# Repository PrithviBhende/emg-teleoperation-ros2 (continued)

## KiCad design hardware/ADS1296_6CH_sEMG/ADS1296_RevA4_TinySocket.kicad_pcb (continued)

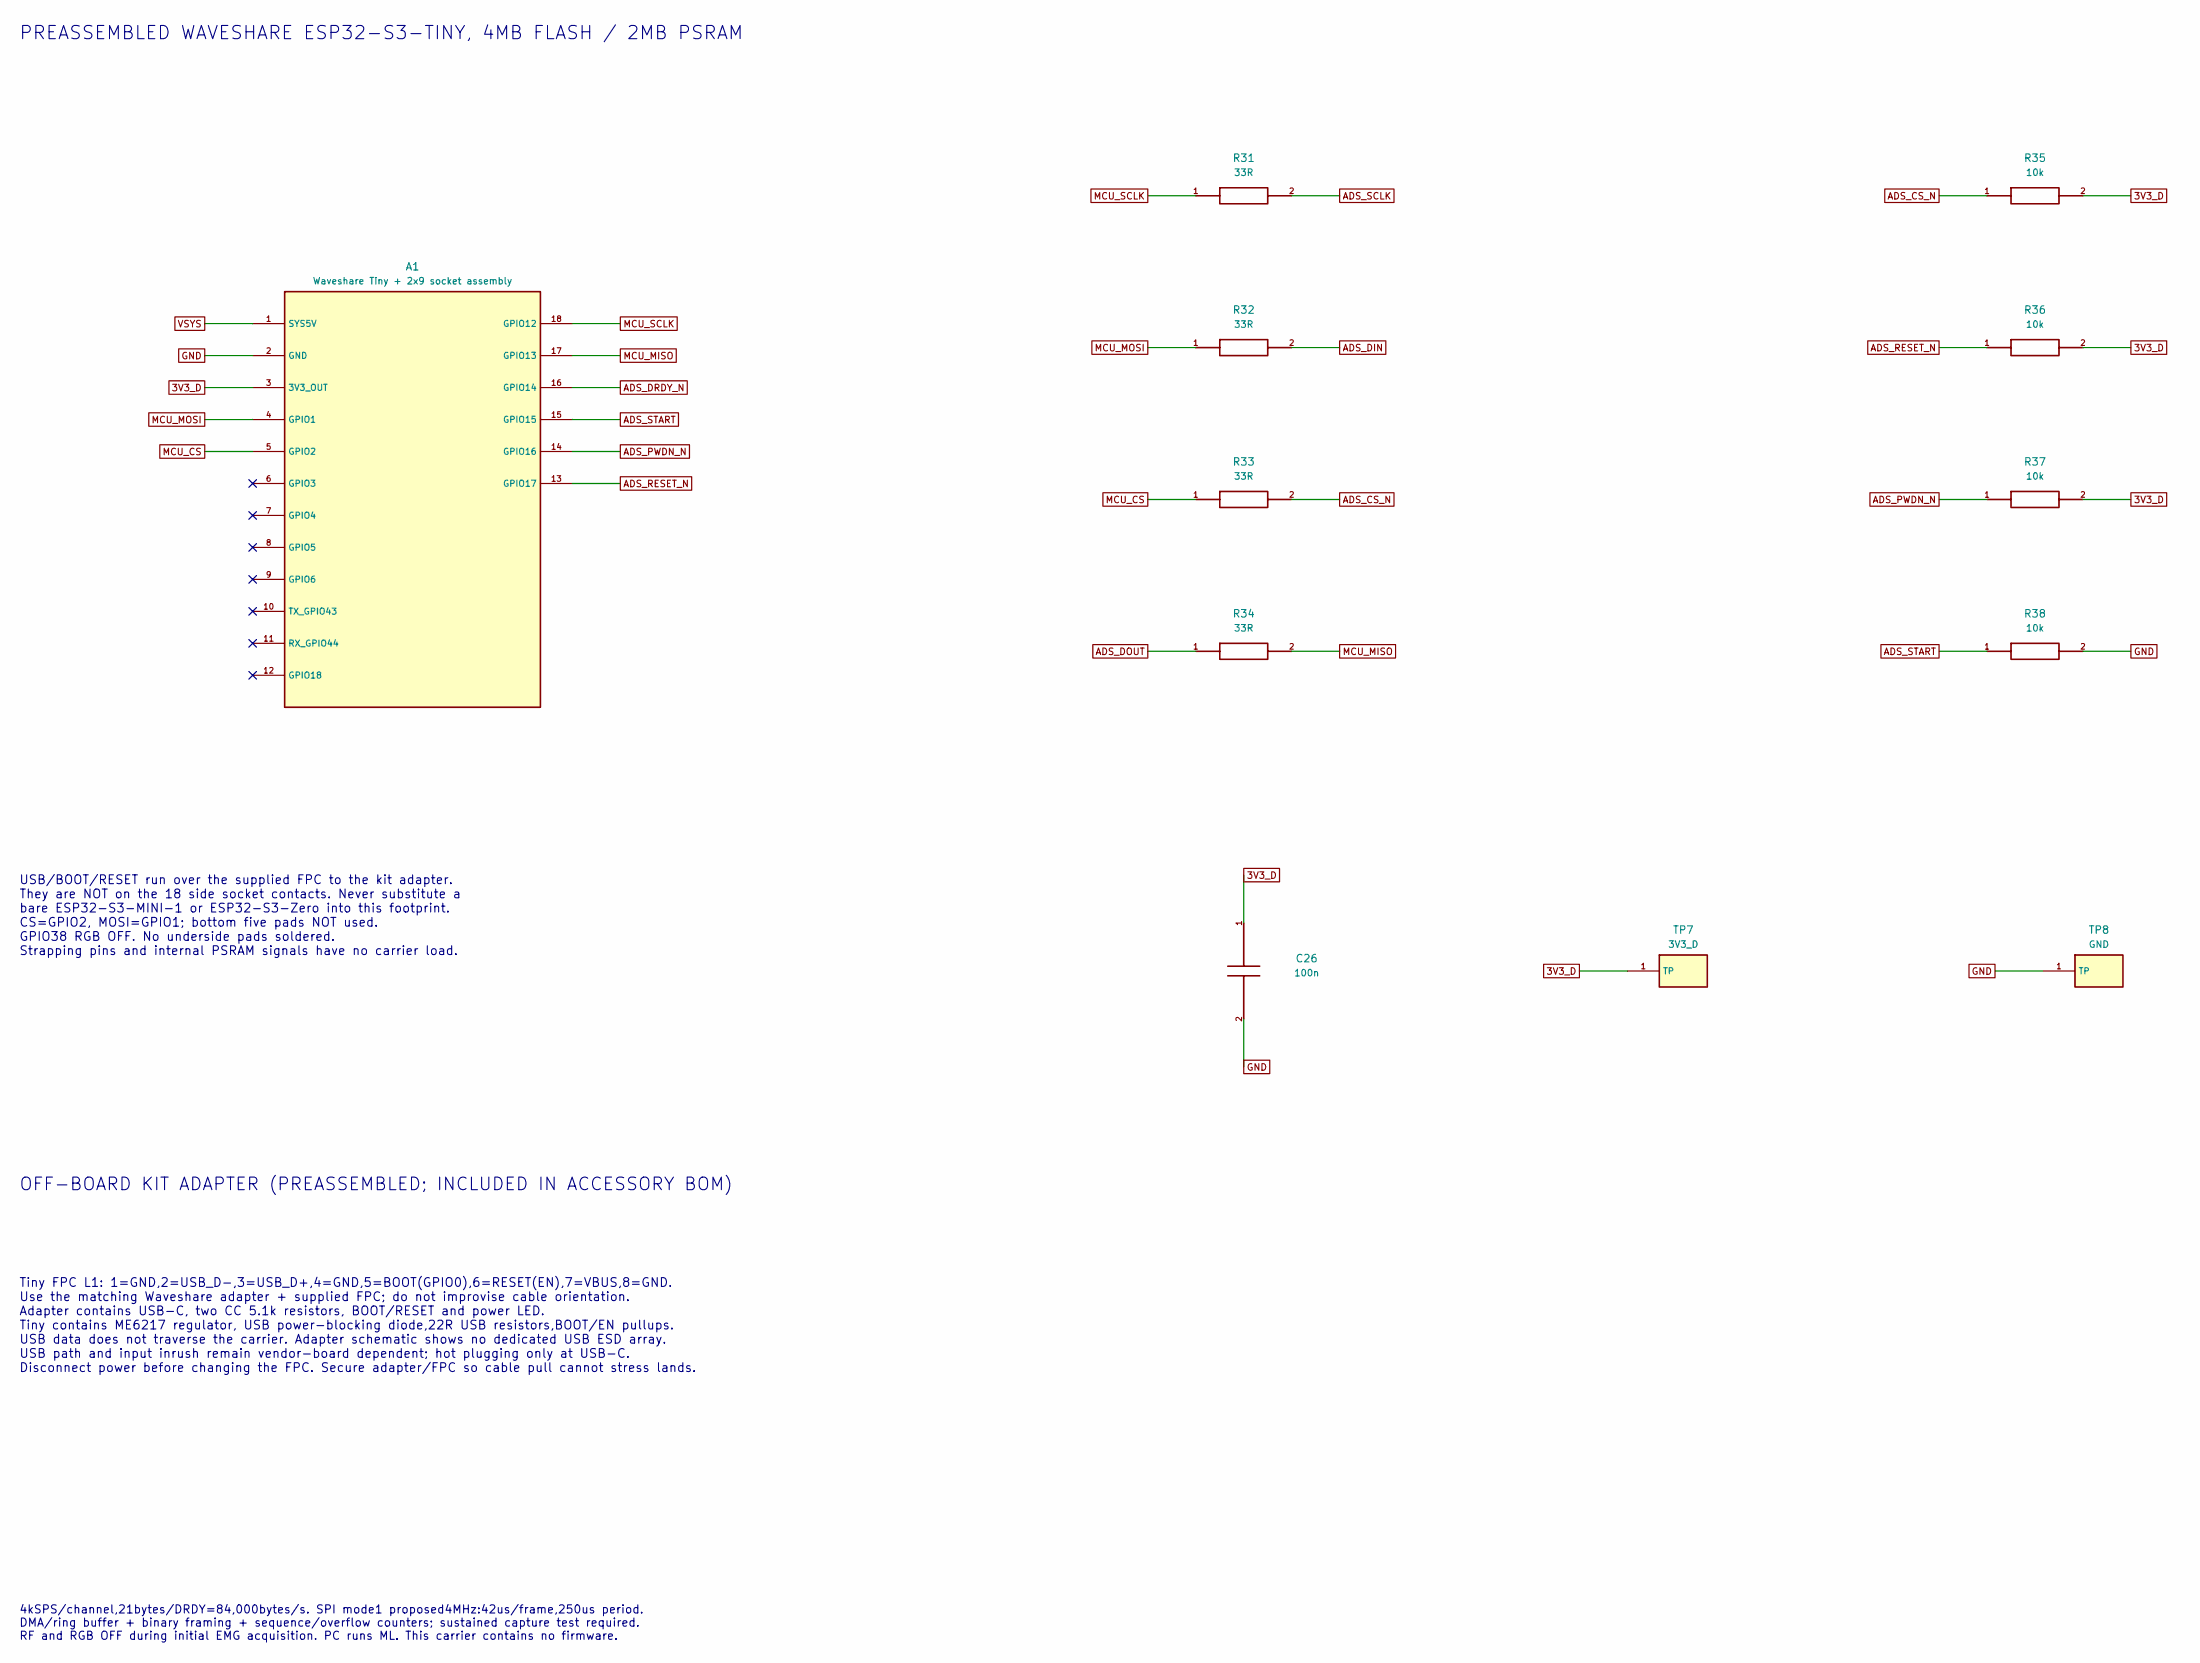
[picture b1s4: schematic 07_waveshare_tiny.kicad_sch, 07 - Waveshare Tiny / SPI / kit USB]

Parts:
A1: Waveshare Tiny + 2x9 socket assembly; Waveshare_ESP32_S3_Tiny_Socket18; MPN ESP32-S3-Tiny-Kit (27070)
C26: 100n; C_0805_2012Metric; MPN C0805C104K4RACTU
R31, R32, R33, R34: 33R; R_0805_2012Metric; MPN RC0805FR-0733RL
R35, R36, R37, R38: 10k; R_0805_2012Metric; MPN RC0805FR-0710KL
TP7: 3V3_D; TestPoint_Pad_D1.5mm
TP8: GND; TestPoint_Pad_D1.5mm

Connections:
3V3_D: A1.3 (3V3_OUT), C26.1, R35.2, R36.2, R37.2, TP7.1; also elsewhere on the board
ADS_CS_N: R33.2, R35.1; also elsewhere on the board
ADS_DIN: R32.2; also elsewhere on the board
ADS_DOUT: R34.1; also elsewhere on the board
ADS_DRDY_N: A1.16 (GPIO14); also elsewhere on the board
ADS_PWDN_N: A1.14 (GPIO16), R37.1; also elsewhere on the board
ADS_RESET_N: A1.13 (GPIO17), R36.1; also elsewhere on the board
ADS_SCLK: R31.2; also elsewhere on the board
ADS_START: A1.15 (GPIO15), R38.1; also elsewhere on the board
GND: A1.2 (GND), C26.2, R38.2, TP8.1; also elsewhere on the board
MCU_CS: A1.5 (GPIO2), R33.1
MCU_MISO: A1.17 (GPIO13), R34.2
MCU_MOSI: A1.4 (GPIO1), R32.1
MCU_SCLK: A1.18 (GPIO12), R31.1
VSYS: A1.1 (SYS5V); also elsewhere on the board

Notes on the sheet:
PREASSEMBLED WAVESHARE ESP32-S3-TINY, 4MB FLASH / 2MB PSRAM
USB/BOOT/RESET run over the supplied FPC to the kit adapter. They are NOT on the 18 side socket contacts. Never substitute a bare ESP32-S3-MINI-1 or ESP32-S3-Zero into this footprint. CS=GPIO2, MOSI=GPIO1; bottom five pads NOT used. GPIO38 RGB OFF. No underside pads soldered. Strapping pins and int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
OFF-BOARD KIT ADAPTER (PREASSEMBLED; INCLUDED IN ACCESSORY BOM)
Tiny FPC L1: 1=GND,2=USB_D-,3=USB_D+,4=GND,5=BOOT(GPIO0),6=RESET(EN),7=VBUS,8=GND. Use the matching Waveshare adapter + supplied FPC; do not improvise cable orientation. Adapter contains USB-C, two CC 5.1k resistors, BOOT/RESET and power LED. Tiny contains ME6217 regulator, USB power-blocking diode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
4kSPS/channel,21bytes/DRDY=84,000bytes/s. SPI mode1 proposed4MHz:42us/frame,250us period. DMA/ring buffer + binary framing + sequence/overflow counters; sustained capture test required. RF and RGB OFF during initial EMG acquisition. PC runs ML. This carrier contains no firmware.

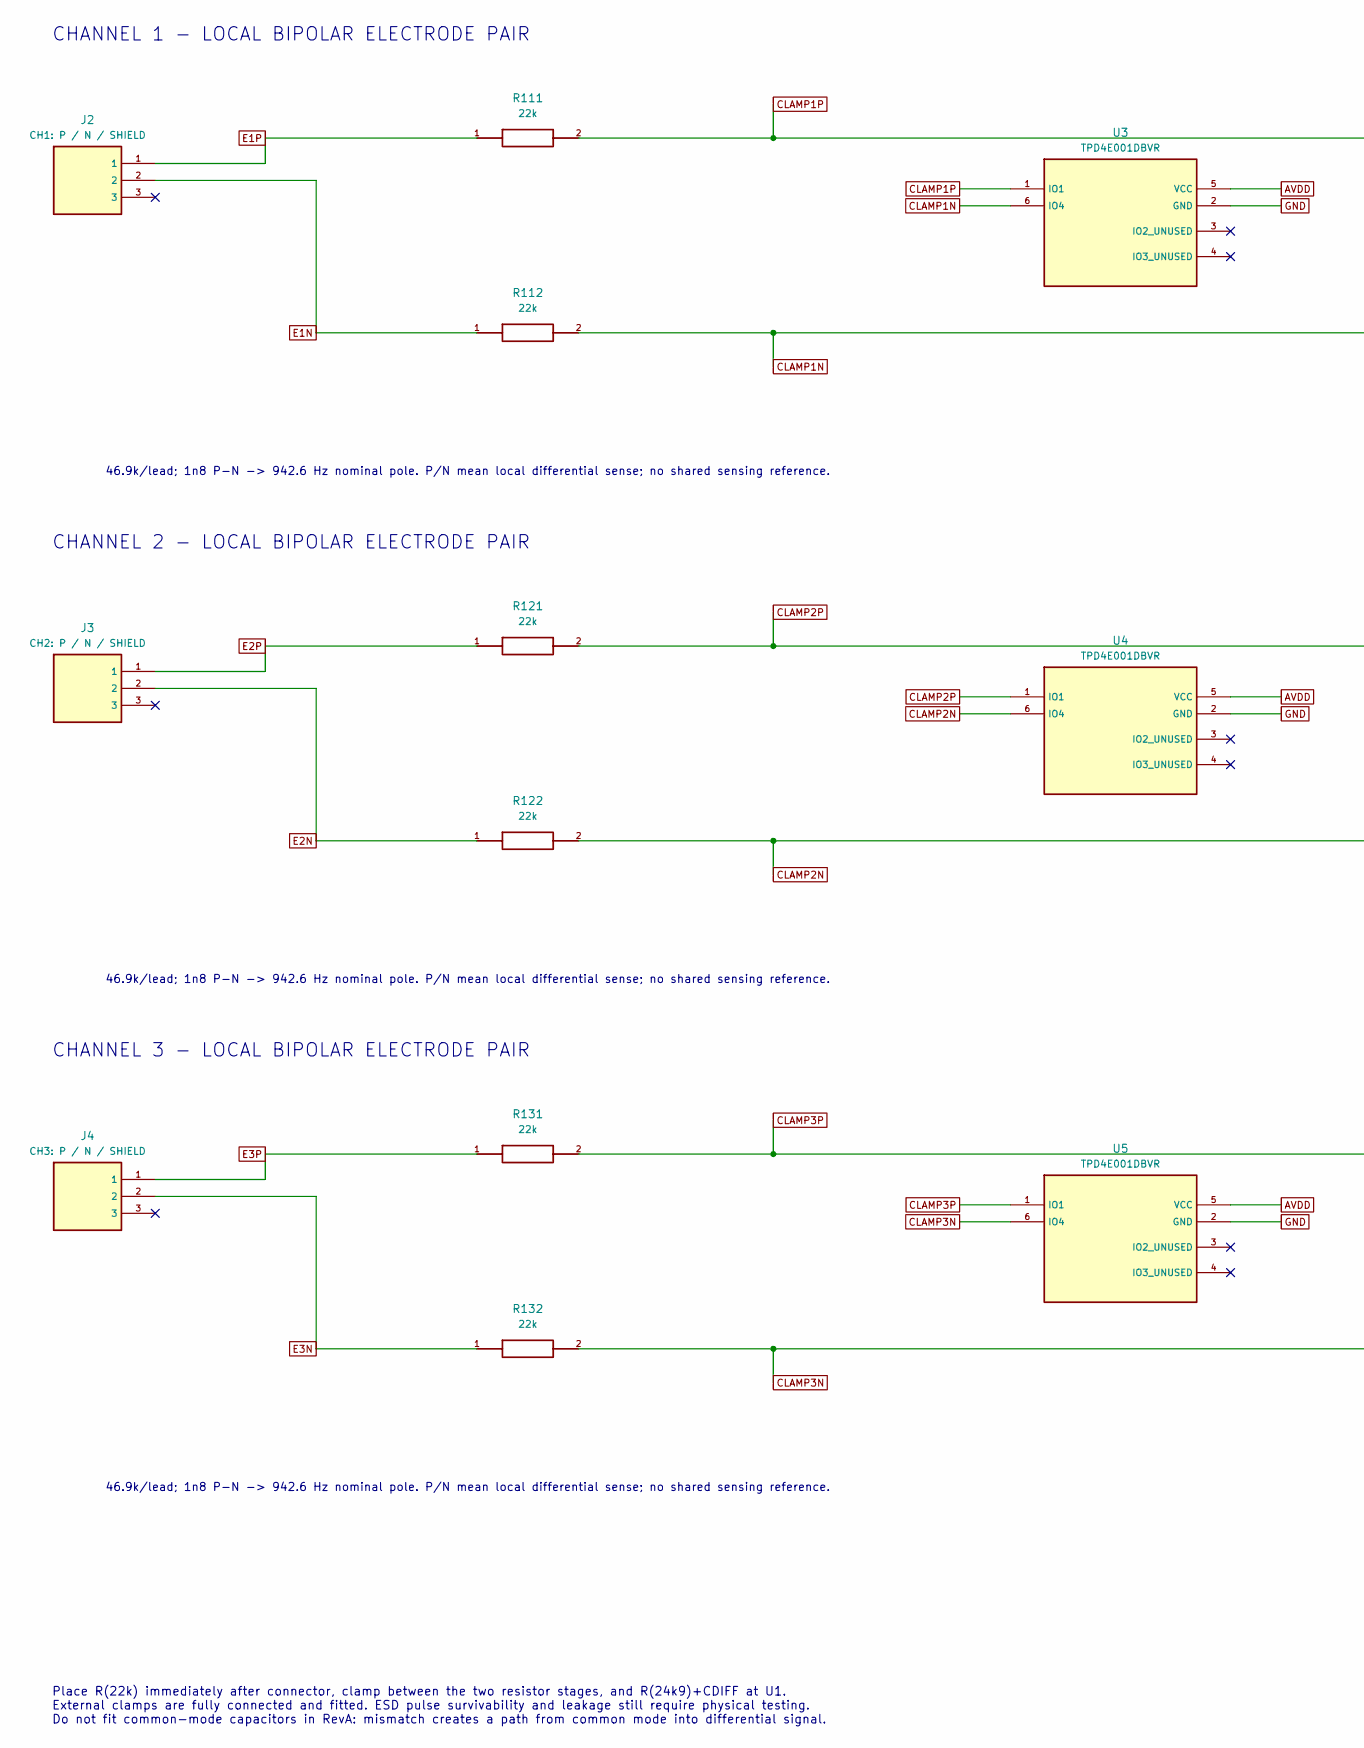
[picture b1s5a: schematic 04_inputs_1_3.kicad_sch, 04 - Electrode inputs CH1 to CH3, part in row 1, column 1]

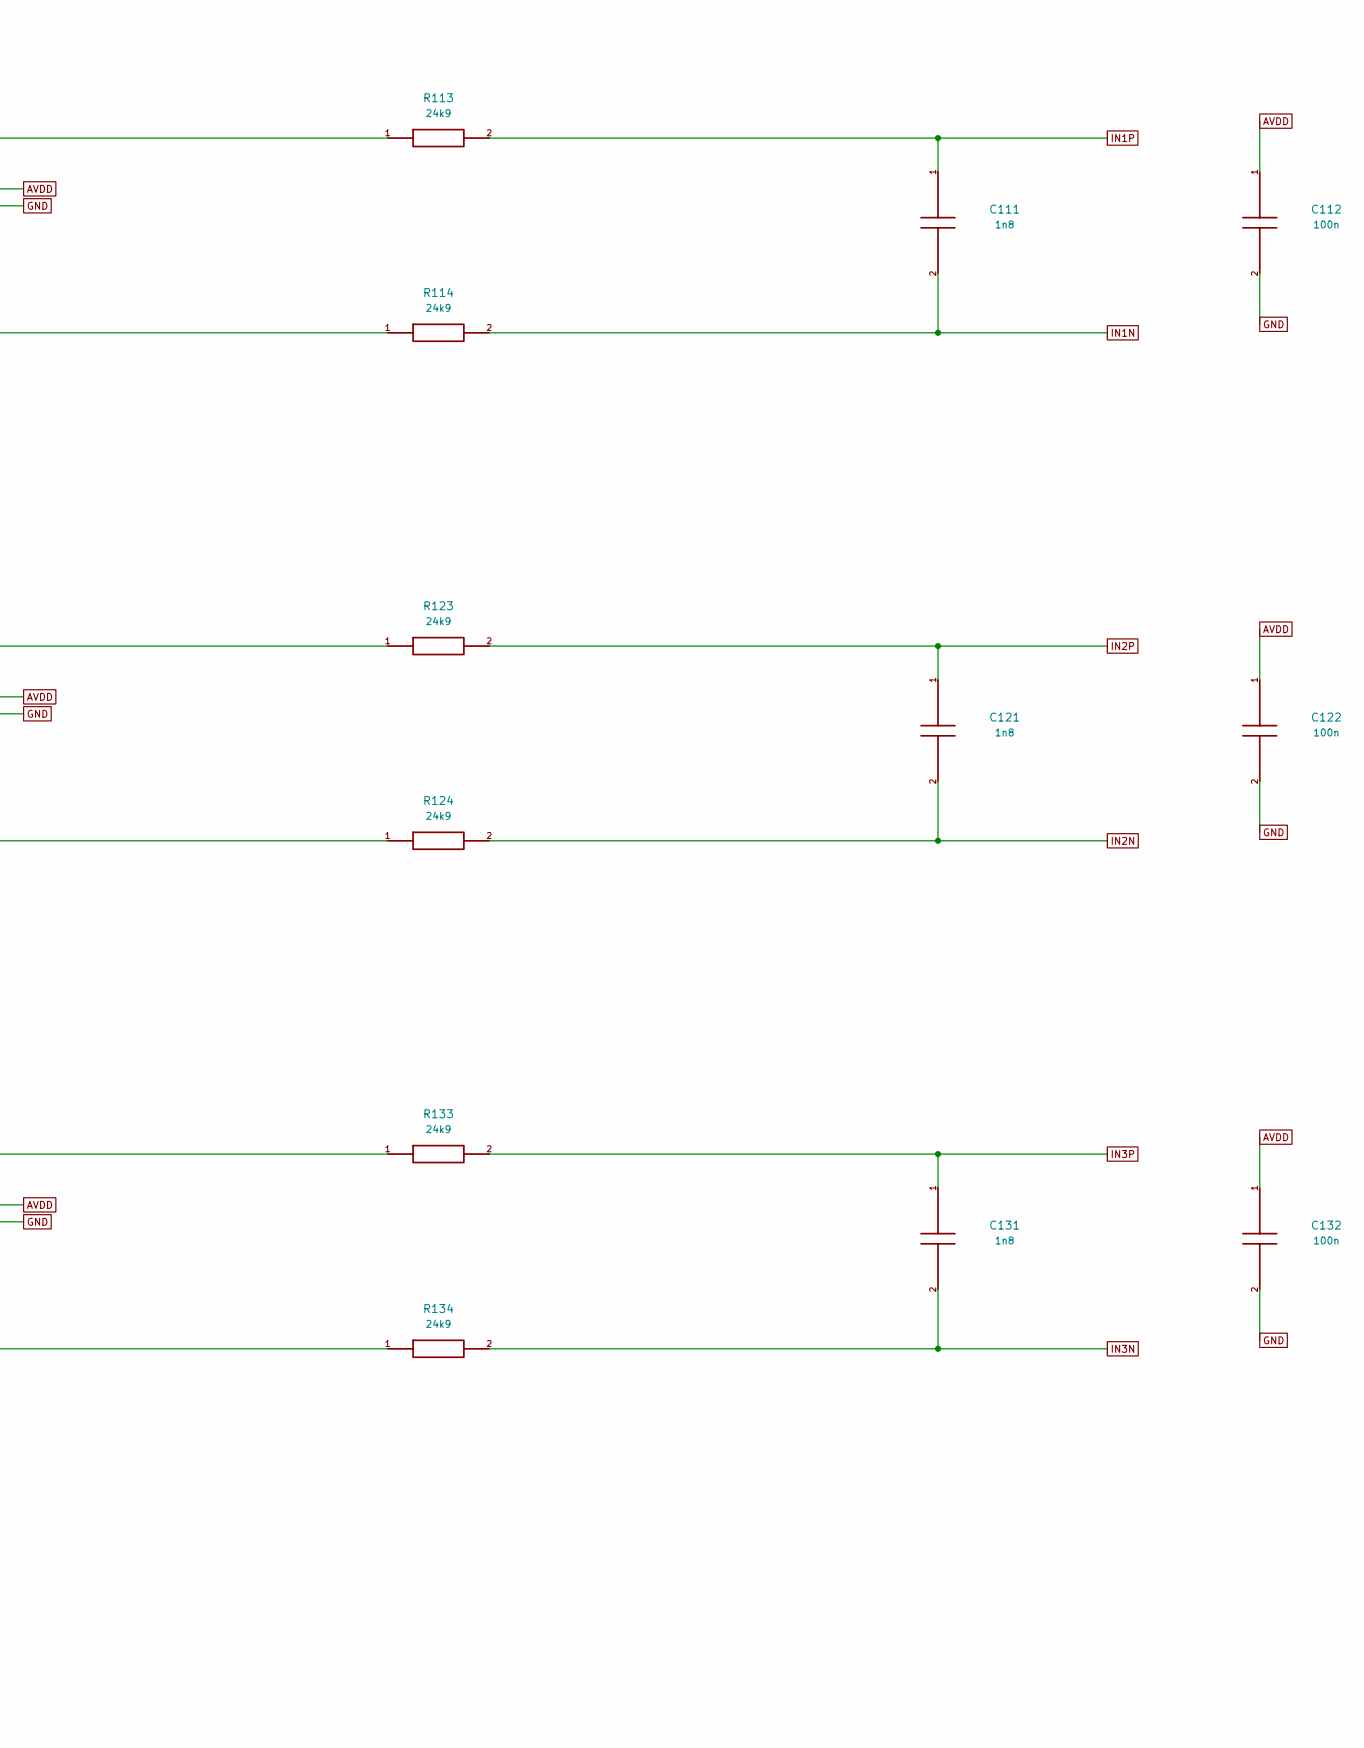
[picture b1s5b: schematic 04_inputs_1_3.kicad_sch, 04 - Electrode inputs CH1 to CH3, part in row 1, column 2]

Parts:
C111, C121, C131: 1n8; C_0805_2012Metric; MPN C0805C182J5GACTU
C112, C122, C132: 100n; C_0805_2012Metric; MPN C0805C104K4RACTU
J2: CH1: P / N / SHIELD; JST_PH_B3B-PH-K_1x03_P2.00mm_Vertical; MPN B3B-PH-K-S(LF)(SN)
J3: CH2: P / N / SHIELD; JST_PH_B3B-PH-K_1x03_P2.00mm_Vertical; MPN B3B-PH-K-S(LF)(SN)
J4: CH3: P / N / SHIELD; JST_PH_B3B-PH-K_1x03_P2.00mm_Vertical; MPN B3B-PH-K-S(LF)(SN)
R111, R112, R121, R122, R131, R132: 22k; R_0805_2012Metric; MPN RT0805BRD0722KL
R113, R114, R123, R124, R133, R134: 24k9; R_0805_2012Metric; MPN RT0805BRD0724K9L
U3, U4, U5: TPD4E001DBVR; SOT-23-6; MPN TPD4E001DBVR

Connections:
AVDD: C112.1, C122.1, C132.1, U3.5 (VCC), U4.5 (VCC), U5.5 (VCC); also elsewhere on the board
CLAMP1N: R112.2, R114.1, U3.6 (IO4)
CLAMP1P: R111.2, R113.1, U3.1 (IO1)
CLAMP2N: R122.2, R124.1, U4.6 (IO4)
CLAMP2P: R121.2, R123.1, U4.1 (IO1)
CLAMP3N: R132.2, R134.1, U5.6 (IO4)
CLAMP3P: R131.2, R133.1, U5.1 (IO1)
E1N: J2.2, R112.1
E1P: J2.1, R111.1
E2N: J3.2, R122.1
E2P: J3.1, R121.1
E3N: J4.2, R132.1
E3P: J4.1, R131.1
GND: C112.2, C122.2, C132.2, U3.2 (GND), U4.2 (GND), U5.2 (GND); also elsewhere on the board
IN1N: C111.2, R114.2; also elsewhere on the board
IN1P: C111.1, R113.2; also elsewhere on the board
IN2N: C121.2, R124.2; also elsewhere on the board
IN2P: C121.1, R123.2; also elsewhere on the board
IN3N: C131.2, R134.2; also elsewhere on the board
IN3P: C131.1, R133.2; also elsewhere on the board

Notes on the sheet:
CHANNEL 1 - LOCAL BIPOLAR ELECTRODE PAIR
46.9k/lead; 1n8 P-N -> 942.6 Hz nominal pole. P/N mean local differential sense; no shared sensing reference.
CHANNEL 2 - LOCAL BIPOLAR ELECTRODE PAIR
CHANNEL 3 - LOCAL BIPOLAR ELECTRODE PAIR
Place R(22k) immediately after connector, clamp between the two resistor stages, and R(24k9)+CDIFF at U1. External clamps are fully connected and fitted. ESD pulse survivability and leakage still require physical testing. Do not fit common-mode capacitors in RevA: mismatch creates a path from commo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

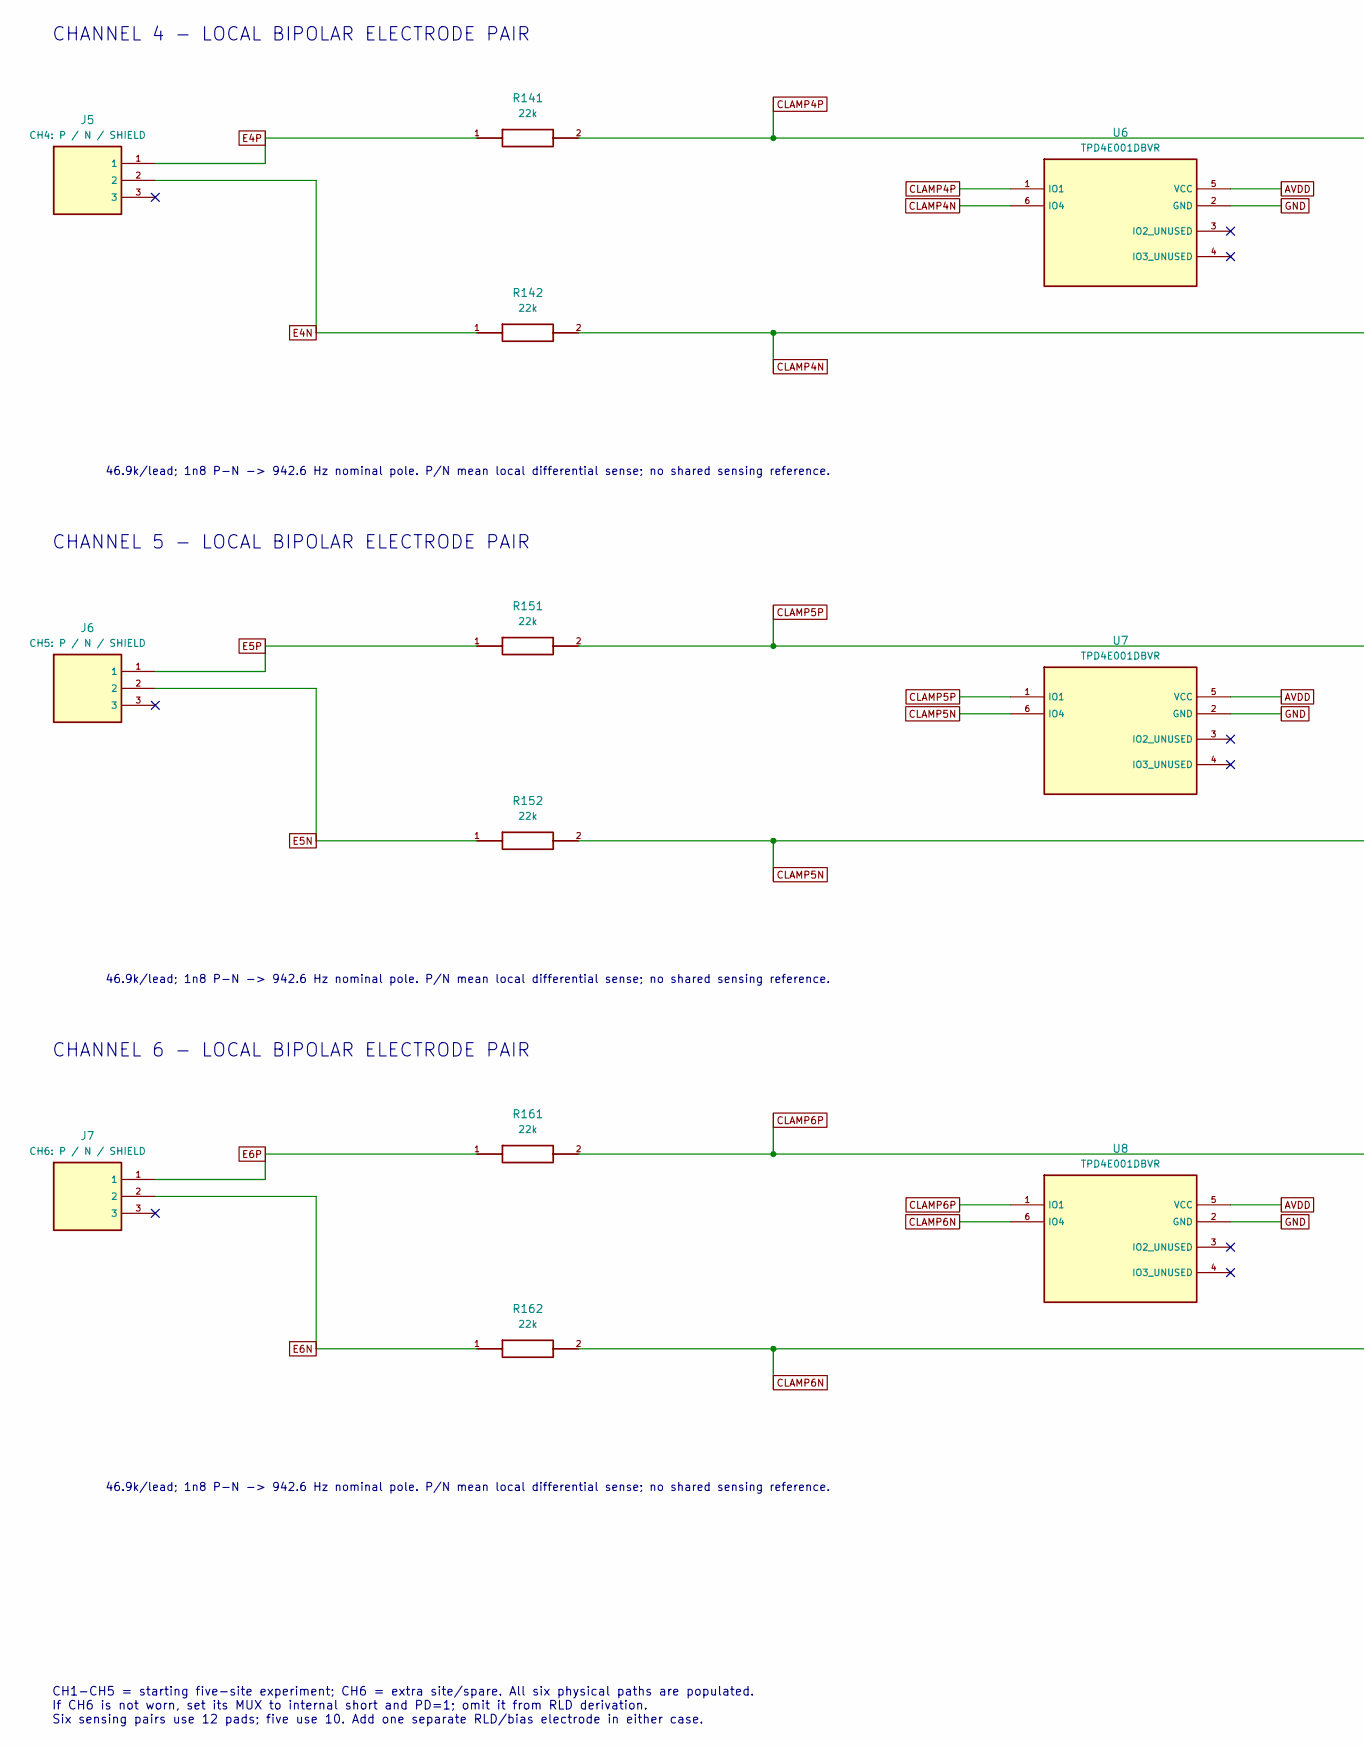
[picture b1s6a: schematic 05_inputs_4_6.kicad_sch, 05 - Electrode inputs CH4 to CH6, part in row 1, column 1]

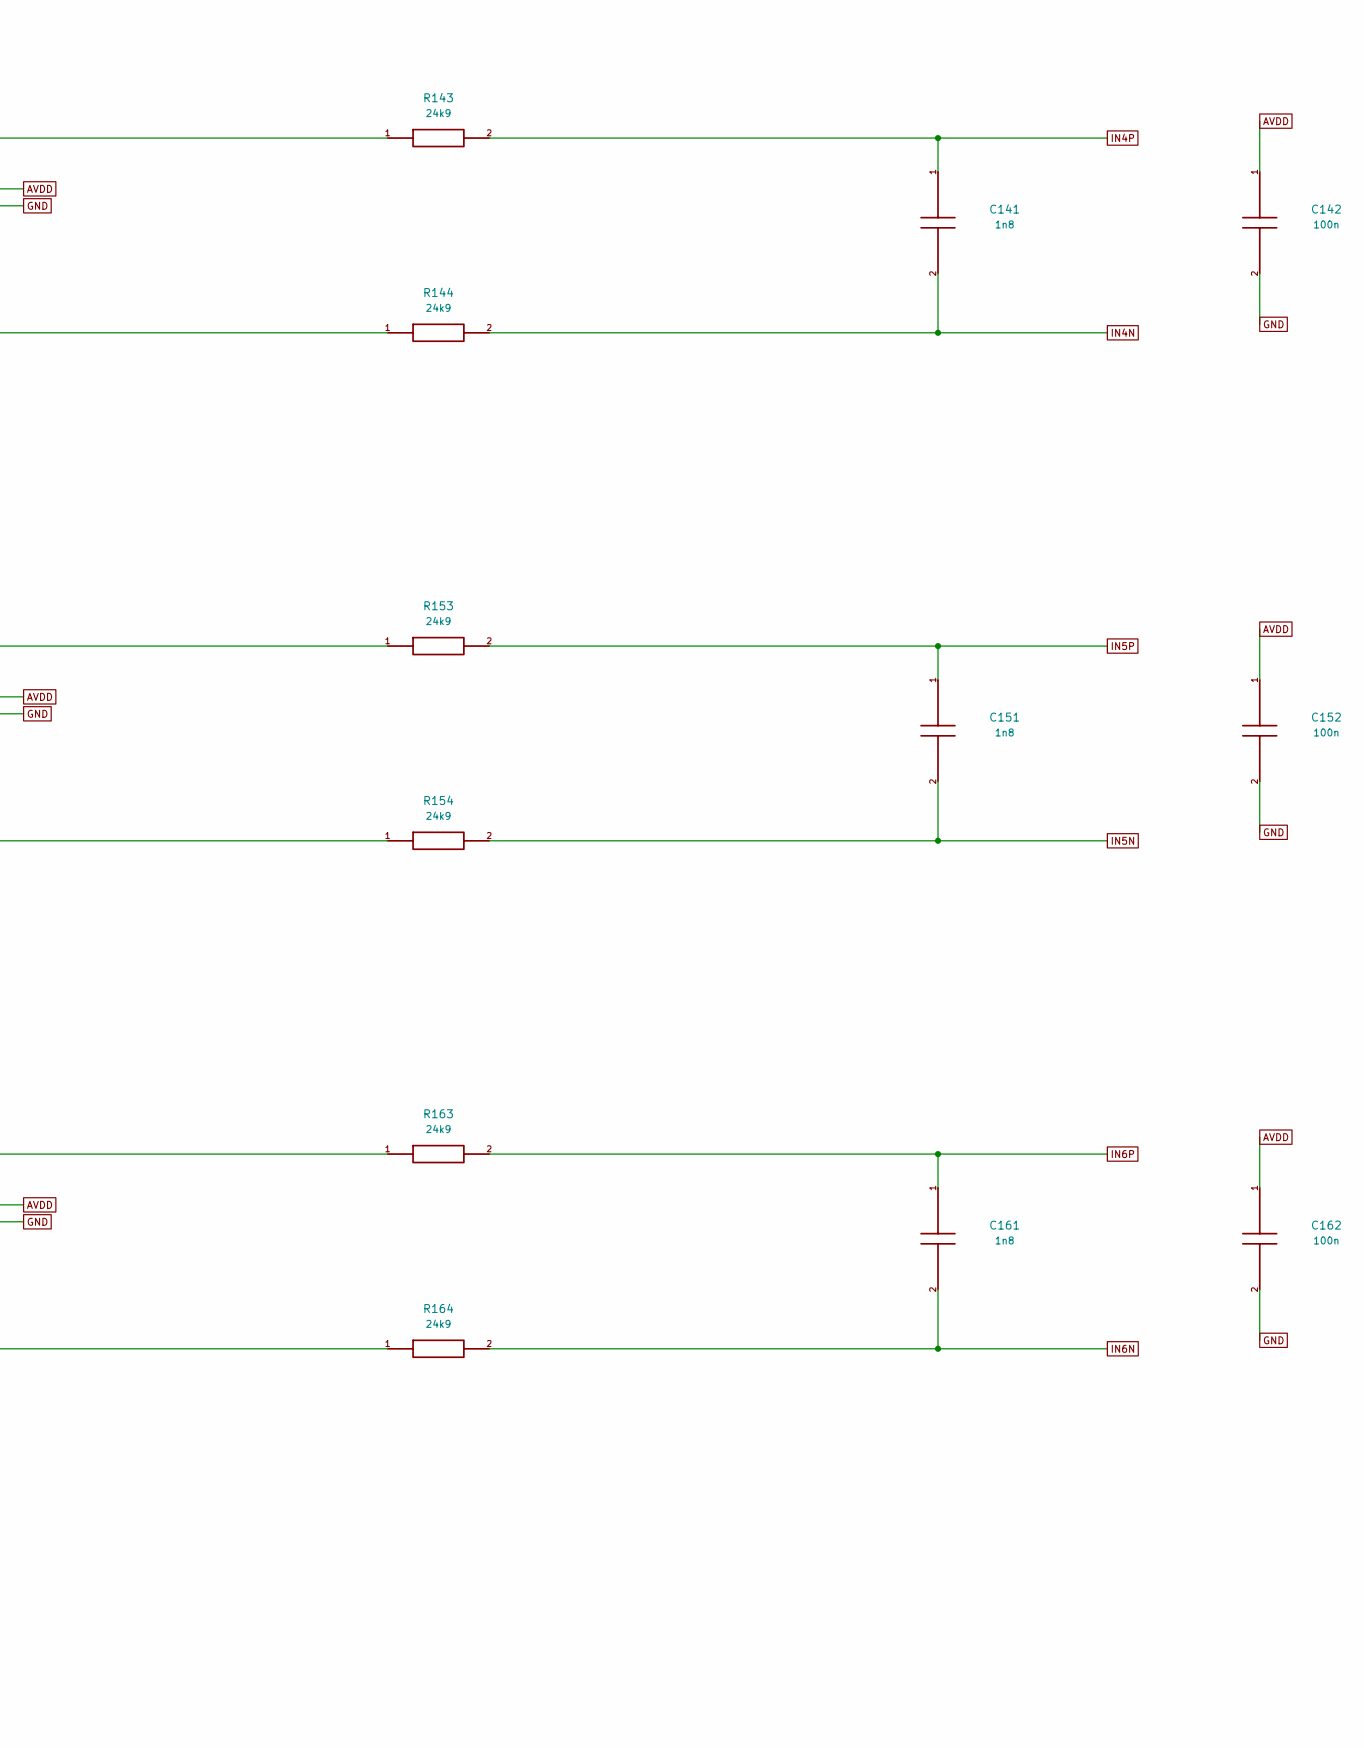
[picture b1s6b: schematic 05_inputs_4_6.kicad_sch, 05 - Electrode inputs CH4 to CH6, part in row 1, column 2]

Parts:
C141, C151, C161: 1n8; C_0805_2012Metric; MPN C0805C182J5GACTU
C142, C152, C162: 100n; C_0805_2012Metric; MPN C0805C104K4RACTU
J5: CH4: P / N / SHIELD; JST_PH_B3B-PH-K_1x03_P2.00mm_Vertical; MPN B3B-PH-K-S(LF)(SN)
J6: CH5: P / N / SHIELD; JST_PH_B3B-PH-K_1x03_P2.00mm_Vertical; MPN B3B-PH-K-S(LF)(SN)
J7: CH6: P / N / SHIELD; JST_PH_B3B-PH-K_1x03_P2.00mm_Vertical; MPN B3B-PH-K-S(LF)(SN)
R141, R142, R151, R152, R161, R162: 22k; R_0805_2012Metric; MPN RT0805BRD0722KL
R143, R144, R153, R154, R163, R164: 24k9; R_0805_2012Metric; MPN RT0805BRD0724K9L
U6, U7, U8: TPD4E001DBVR; SOT-23-6; MPN TPD4E001DBVR

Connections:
AVDD: C142.1, C152.1, C162.1, U6.5 (VCC), U7.5 (VCC), U8.5 (VCC); also elsewhere on the board
CLAMP4N: R142.2, R144.1, U6.6 (IO4)
CLAMP4P: R141.2, R143.1, U6.1 (IO1)
CLAMP5N: R152.2, R154.1, U7.6 (IO4)
CLAMP5P: R151.2, R153.1, U7.1 (IO1)
CLAMP6N: R162.2, R164.1, U8.6 (IO4)
CLAMP6P: R161.2, R163.1, U8.1 (IO1)
E4N: J5.2, R142.1
E4P: J5.1, R141.1
E5N: J6.2, R152.1
E5P: J6.1, R151.1
E6N: J7.2, R162.1
E6P: J7.1, R161.1
GND: C142.2, C152.2, C162.2, U6.2 (GND), U7.2 (GND), U8.2 (GND); also elsewhere on the board
IN4N: C141.2, R144.2; also elsewhere on the board
IN4P: C141.1, R143.2; also elsewhere on the board
IN5N: C151.2, R154.2; also elsewhere on the board
IN5P: C151.1, R153.2; also elsewhere on the board
IN6N: C161.2, R164.2; also elsewhere on the board
IN6P: C161.1, R163.2; also elsewhere on the board

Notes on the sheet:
CHANNEL 4 - LOCAL BIPOLAR ELECTRODE PAIR
46.9k/lead; 1n8 P-N -> 942.6 Hz nominal pole. P/N mean local differential sense; no shared sensing reference.
CHANNEL 5 - LOCAL BIPOLAR ELECTRODE PAIR
CHANNEL 6 - LOCAL BIPOLAR ELECTRODE PAIR
CH1-CH5 = starting five-site experiment; CH6 = extra site/spare. All six physical paths are populated. If CH6 is not worn, set its MUX to internal short and PD=1; omit it from RLD derivation. Six sensing pairs use 12 pads; five use 10. Add one separate RLD/bias electrode in either case.

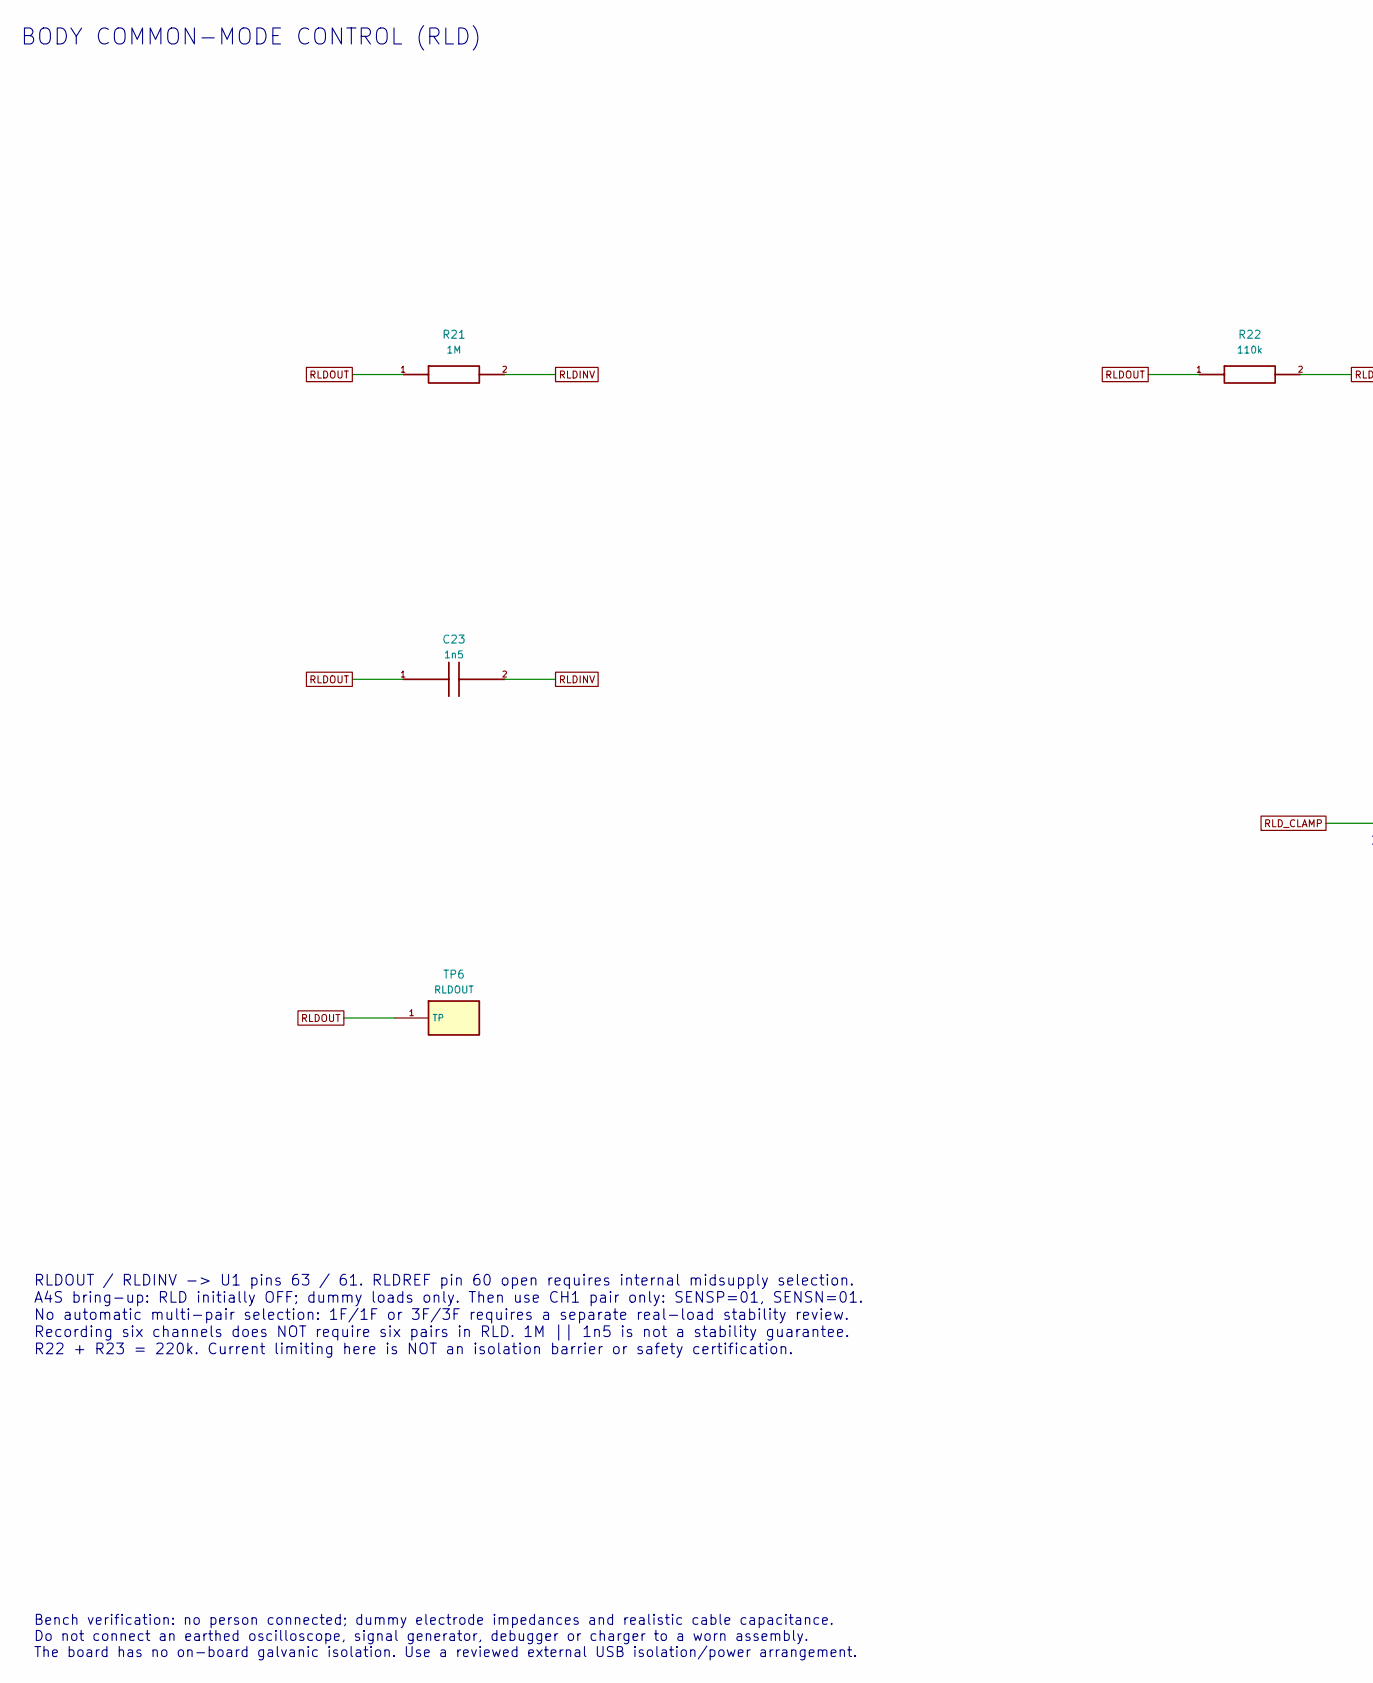
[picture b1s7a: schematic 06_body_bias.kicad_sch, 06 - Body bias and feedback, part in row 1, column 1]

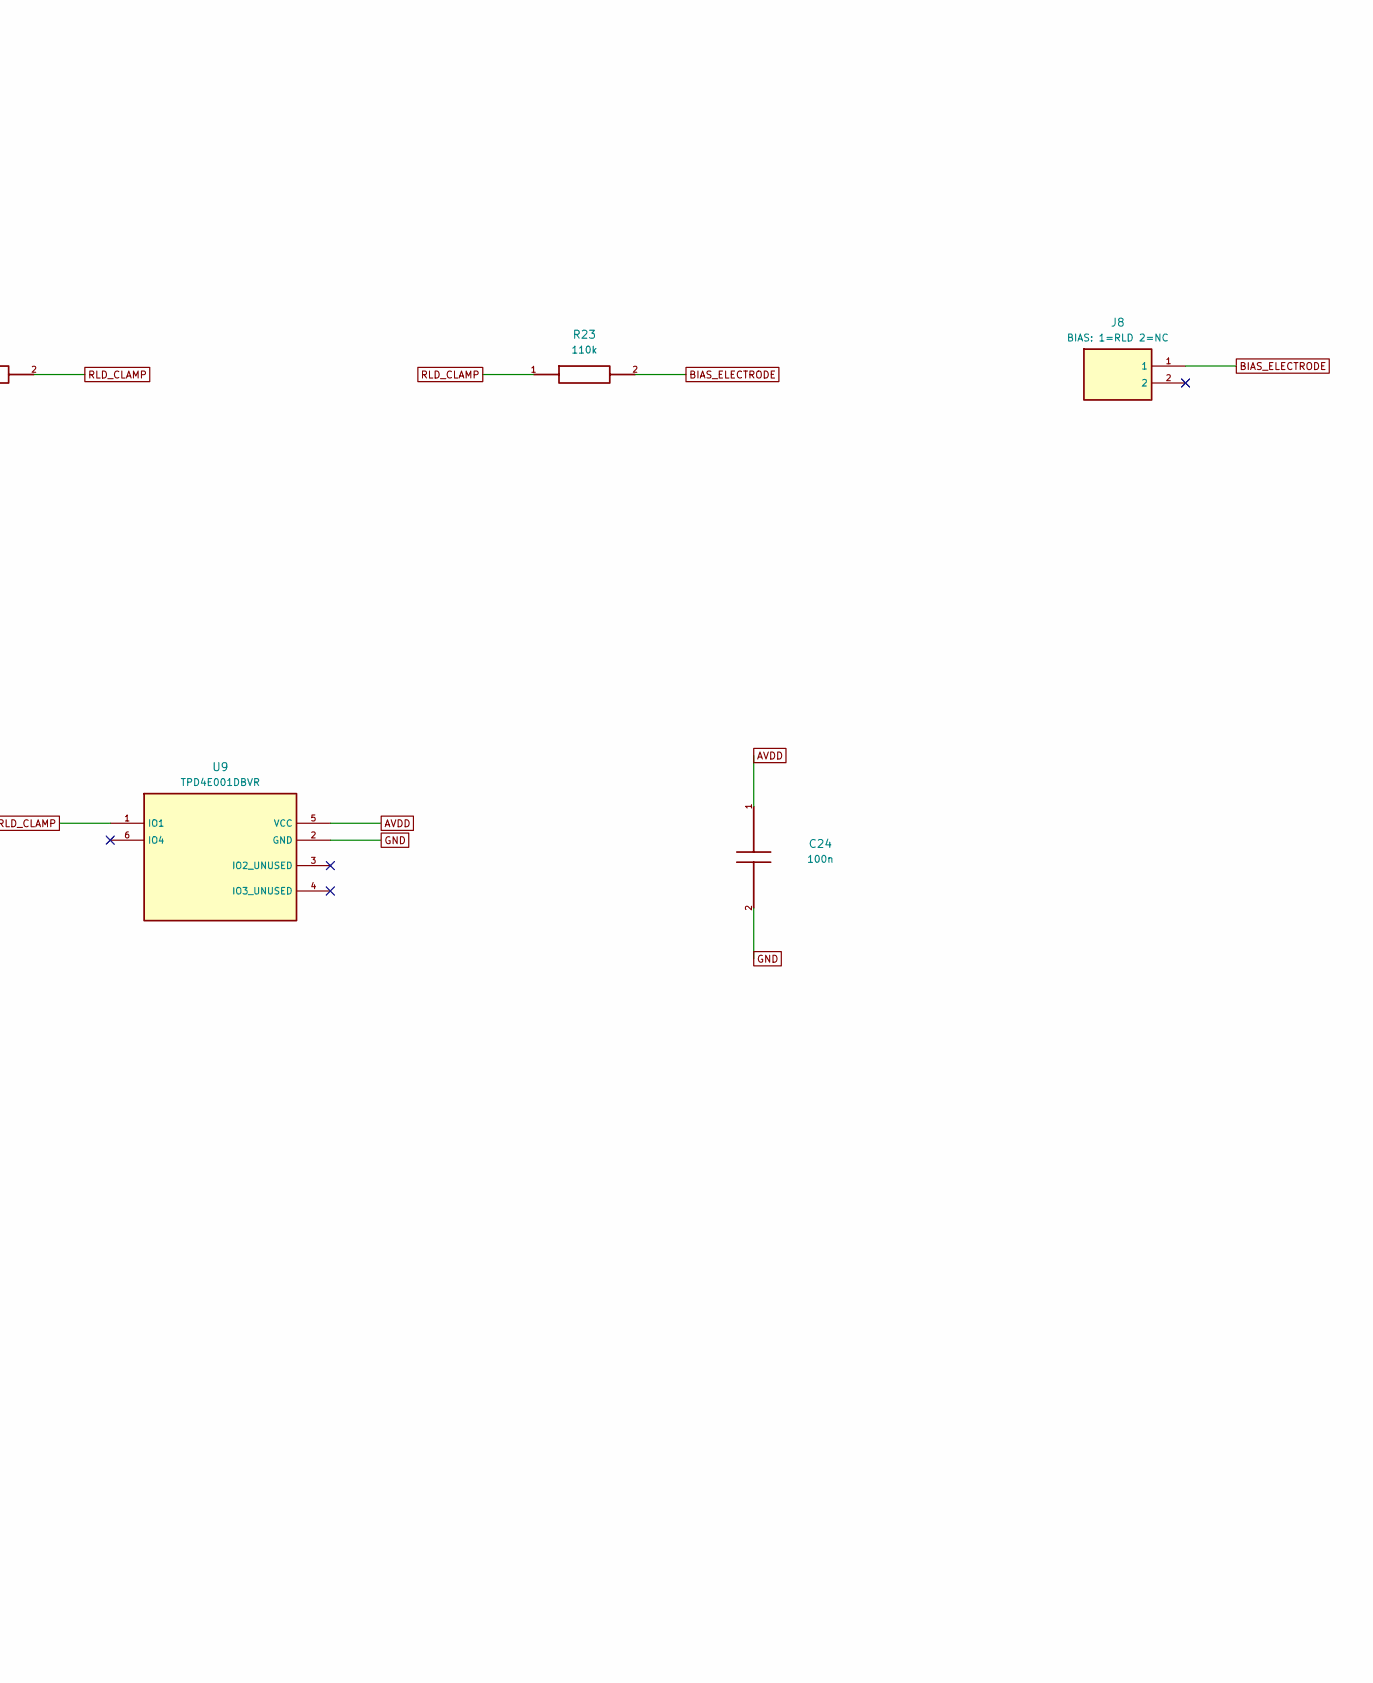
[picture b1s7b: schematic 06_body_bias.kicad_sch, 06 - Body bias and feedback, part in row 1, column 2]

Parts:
C23: 1n5; C_0805_2012Metric; MPN C0805C152J5GACTU
C24: 100n; C_0805_2012Metric; MPN C0805C104K4RACTU
J8: BIAS: 1=RLD 2=NC; JST_PH_B2B-PH-K_1x02_P2.00mm_Vertical; MPN B2B-PH-K-S(LF)(SN)
R21: 1M; R_0805_2012Metric; MPN RC0805FR-071ML
R22, R23: 110k; R_0805_2012Metric; MPN RC0805FR-07110KL
TP6: RLDOUT; TestPoint_Pad_D1.5mm
U9: TPD4E001DBVR; SOT-23-6; MPN TPD4E001DBVR

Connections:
AVDD: C24.1, U9.5 (VCC); also elsewhere on the board
BIAS_ELECTRODE: J8.1, R23.2
GND: C24.2, U9.2 (GND); also elsewhere on the board
RLDINV: C23.2, R21.2; also elsewhere on the board
RLDOUT: C23.1, R21.1, R22.1, TP6.1; also elsewhere on the board
RLD_CLAMP: R22.2, R23.1, U9.1 (IO1)

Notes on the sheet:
BODY COMMON-MODE CONTROL (RLD)
RLDOUT / RLDINV -> U1 pins 63 / 61. RLDREF pin 60 open requires internal midsupply selection. A4S bring-up: RLD initially OFF; dummy loads only. Then use CH1 pair only: SENSP=01, SENSN=01. No automatic multi-pair selection: 1F/1F or 3F/3F requires a separate real-load stability review. Recording si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
Bench verification: no person connected; dummy electrode impedances and realistic cable capacitance. Do not connect an earthed oscilloscope, signal generator, debugger or charger to a worn assembly. The board has no on-board galvanic isolation. Use a reviewed external USB isolation/power arrangemen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
